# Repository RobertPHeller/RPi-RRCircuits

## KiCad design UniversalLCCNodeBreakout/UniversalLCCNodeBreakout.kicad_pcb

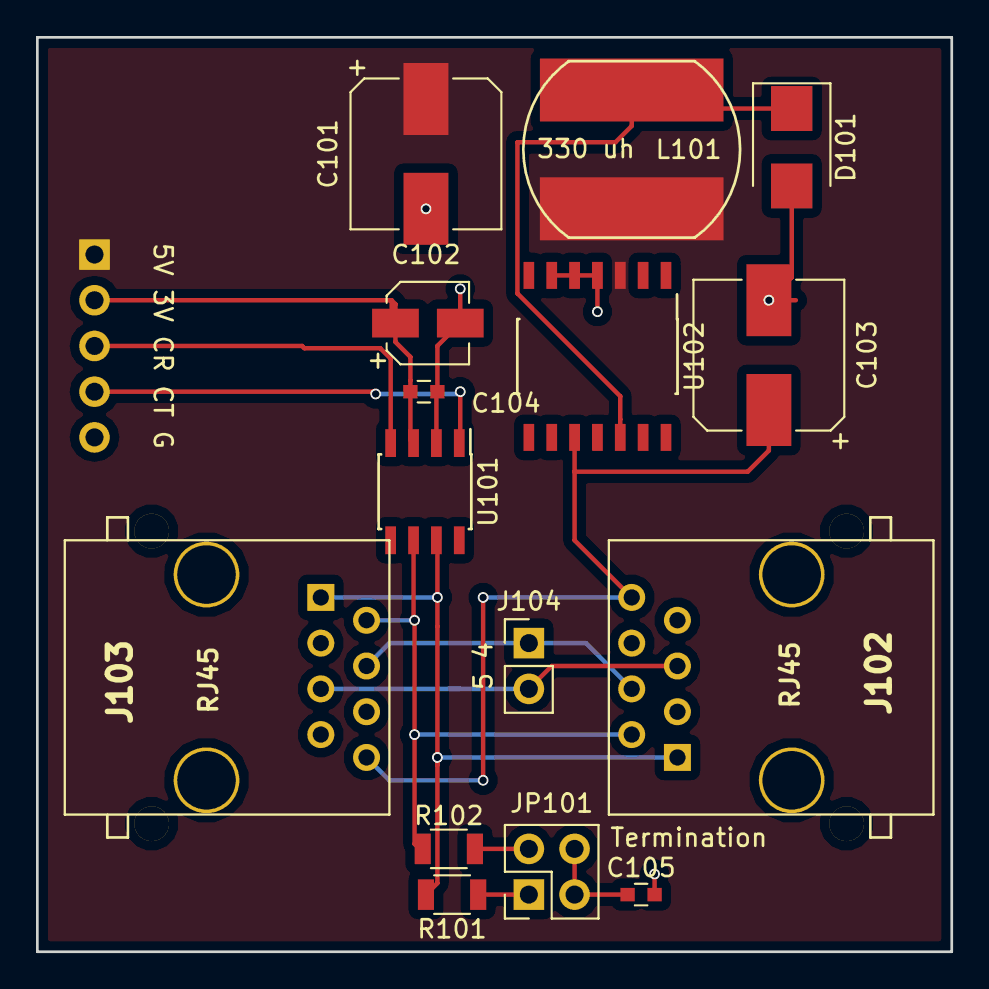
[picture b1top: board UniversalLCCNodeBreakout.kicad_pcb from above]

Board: 2 copper layers, 50.8 x 50.8 mm, 16 parts (1 on the bottom side), 14 nets.

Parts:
C101: 220 uf 25V; CP_Elec_8x10
C102: .1 uf; C_0603
C103: 22 uf 100V; CP_Elec_8x10
C104: 15 uf 15V; CP_Elec_4x5.7
C105: 47 nf; C_0603
D101: CMSH1-60 TR13; D_SMB
J101: 5V 3V CR CT G; Pin_Header_Straight_1x05_Pitch2.54mm
J102, J103: RJ45; RJ45_8N-S
J104: 5 4; Socket_Strip_Straight_1x02_Pitch2.54mm
JP101: Termination; Pin_Header_Straight_2x02_Pitch2.54mm
L101: 330 uh; SRN1060
R101, R102: 60 Ohms; R_1206
U101: TCAN332DR; SOIC-8_3.9x4.9mm_Pitch1.27mm
U102: LM2574N-5; SOIC-14_7.4x8.7mm_Pitch1.27mm

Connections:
+3V3: C102.1, C104.1, J101.2, U101.3
+5V: C101.1, J101.1, L101.2, U102.3
/CANH: J102.1, J103.1, R101.1, U101.7
/CANL: J102.2, J103.2, R102.1, U101.6
/CAN_RX: J101.3, U101.4
/CAN_TX: J101.4, U101.1
CAN +12V: C103.1, J102.8, J103.8, U102.10
GND: C101.2, C102.2, C103.2, C104.2, C105.2, D101.2, J101.5, J102.3, J102.6, J102.7, J103.3, J103.6, J103.7, U101.2, U102.4, U102.5, U102.6
unnamed: C105.1, JP101.3, JP101.4
unnamed: D101.1, L101.1, U102.12
unnamed: J102.4, J103.4, J104.1
unnamed: J102.5, J103.5, J104.2
unnamed: JP101.1, R101.2
unnamed: JP101.2, R102.2

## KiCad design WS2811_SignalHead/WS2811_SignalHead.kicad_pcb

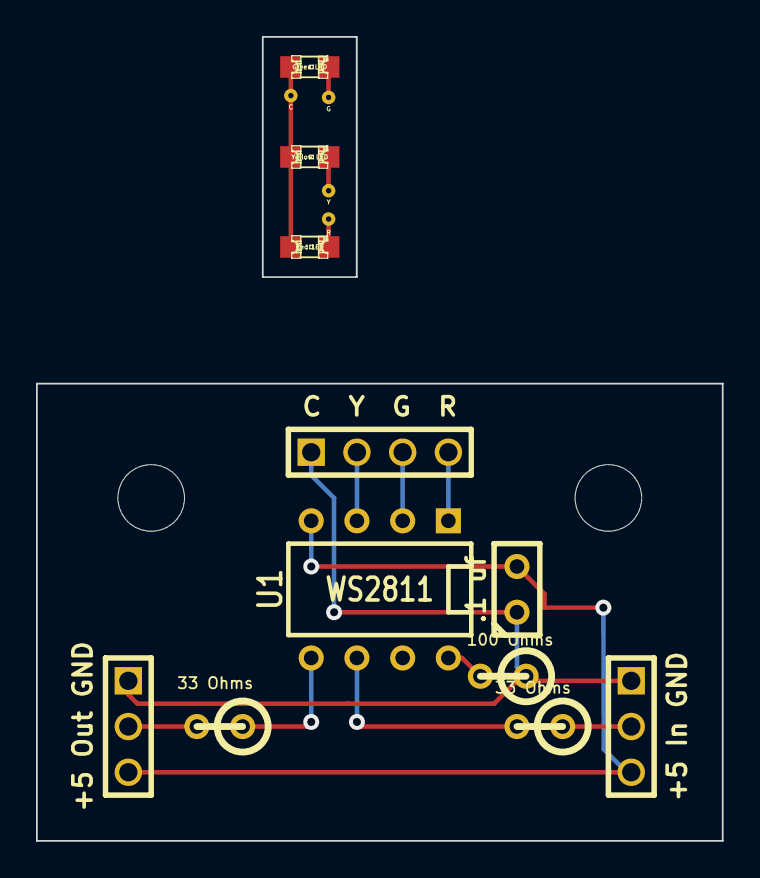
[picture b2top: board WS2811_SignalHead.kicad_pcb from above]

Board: 2 copper layers, 38.1 x 44.7 mm, 17 parts (0 on the bottom side), 14 nets.

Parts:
C1: .1 uf; C1
D1: Red LED; LED-0805
D2: Yellow LED; LED-0805
D3: Green LED; LED-0805
K1: +5 In GND; ScrewTerm_2.54-3
K2: +5 Out GND; ScrewTerm_2.54-3
MH: MountingHole_3-7mm_RevA_Date21Jun2010
MH#2: MountingHole_3-7mm_RevA_Date21Jun2010
P1: C Y G R; ScrewTerm_2.54-4
P2: C; microterm
P3: R; microterm
P4: Y; microterm
P5: G; microterm
R1, R3: 33 Ohms; R1
R2: 100 Ohms; R1
U1: WS2811; DIP-8__300

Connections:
+5V: C1.1, K1.1, K2.1, P1.1, R2.1
Common (+): D1.1, D2.1, D3.1, P2.1
GND: C1.2, K1.3, K2.3, U1.4
Green: D3.2, P5.1
unnamed: R1.2, U1.6
unnamed: K1.2, R1.1
unnamed: K2.2, R3.2
unnamed: R3.1, U1.5
unnamed: R2.2, U1.8
unnamed: P1.2, U1.3
unnamed: P1.3, U1.2
unnamed: P1.4, U1.1
Red: D1.2, P3.1
Yellow: D2.2, P4.1

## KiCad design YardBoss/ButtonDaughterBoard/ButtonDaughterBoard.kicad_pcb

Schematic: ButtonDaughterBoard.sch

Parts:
C1: CP1
C2, C3, C4, C5: .1 uf
C6, C7, C8, C9, C10, C11, C12, C13, C14, C15, C16, C17, C18, C19, C20, C21: 10 nf
J1: I2CIN
J2: I2COUT
P1: 2 1 0
P2: GND 00 01 02 03
P3: GND 17 16 15 14
P4: 13 12 11 10 GND
P5: 04 05 06 07 GND
R1, R2, R3, R4, R5, R6, R7, R8, R9, R10, R11, R12, R13, R14, R15, R16: 10K Ohms
RR1: 10K Ohms
U1: MCP23017
U2, U3, U4: 74HC14

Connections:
+3.3V: C1.1, C2.1, C3.1, C4.1, C5.1, J1.4, J2.2, R1.2, R2.2, R3.2, R4.2, R5.2, R6.2, R7.2, R8.2, R9.2, R10.2, R11.2, R12.2, R13.2, R14.2, R15.2, R16.2, RR1.1 (COM), U1.9 (Vdd), U2.14 (VCC), U3.14 (VCC), U4.14 (VCC)
+5V: J1.5, J2.1
/B0.0: C13.1, P2.4, R8.1, U3.9
/B0.1: C12.1, P2.3, R7.1, U3.5
/B0.2: C11.1, P2.2, R6.1, U3.3
/B0.3: C10.1, P2.1, R5.1, U3.1
/B0.4: C9.1, P5.5, R4.1, U2.13
/B0.5: C8.1, P5.4, R3.1, U2.11
/B0.6: C7.1, P5.3, R2.1, U2.9
/B0.7: C6.1, P5.2, R1.1, U2.5
/B1.0: C21.1, P4.4, R16.1, U4.13
/B1.1: C20.1, P4.3, R15.1, U4.11
/B1.2: C19.1, P4.2, R14.1, U4.9
/B1.3: C18.1, P4.1, R13.1, U4.5
/B1.4: C17.1, P3.5, R12.1, U4.3
/B1.5: C16.1, P3.4, R11.1, U4.1
/B1.6: C15.1, P3.3, R10.1, U3.13
/B1.7: C14.1, P3.2, R9.1, U3.11
GND: C1.2, C2.2, C3.2, C4.2, C5.2, C6.2, C7.2, C8.2, C9.2, C10.2, C11.2, C12.2, C13.2, C14.2, C15.2, C16.2, C17.2, C18.2, C19.2, C20.2, C21.2, J1.1, J2.5, P1.1, P1.3, P1.5, P2.5, P3.1, P4.5, P5.1, U1.10 (Vss), U2.1, U2.3, U2.7 (GND), U3.7 (GND), U4.7 (GND)
unnamed: U1.2 (GP1.1), U4.10
unnamed: U1.3 (GP1.2), U4.8
unnamed: U1.4 (GP1.3), U4.6
unnamed: U1.5 (GP1.4), U4.4
unnamed: U1.6 (GP1.5), U4.2
unnamed: U1.7 (GP1.6), U3.12
unnamed: U1.8 (GP1.7), U3.10
unnamed: U1.21 (GP0.0), U3.8
unnamed: U1.22 (GP0.1), U3.6
unnamed: U1.23 (GP0.2), U3.4
unnamed: U1.1 (Gp1.0), U4.12
unnamed: P1.2, RR1.3, U1.17 (A2)
unnamed: P1.4, RR1.4, U1.16 (A1)
unnamed: P1.6, RR1.5, U1.15 (A0)
unnamed: U1.24 (GP0.3), U3.2
unnamed: U1.25 (GP0.4), U2.12
unnamed: U1.26 (GP0.5), U2.10
unnamed: U1.27 (GP0.6), U2.8
unnamed: U1.28 (GP0.7), U2.6
unnamed: RR1.2, U1.18 (Reset)
SCL: J1.2, J2.4, U1.12 (SCL)
SDA: J1.3, J2.3, U1.13 (SDA)

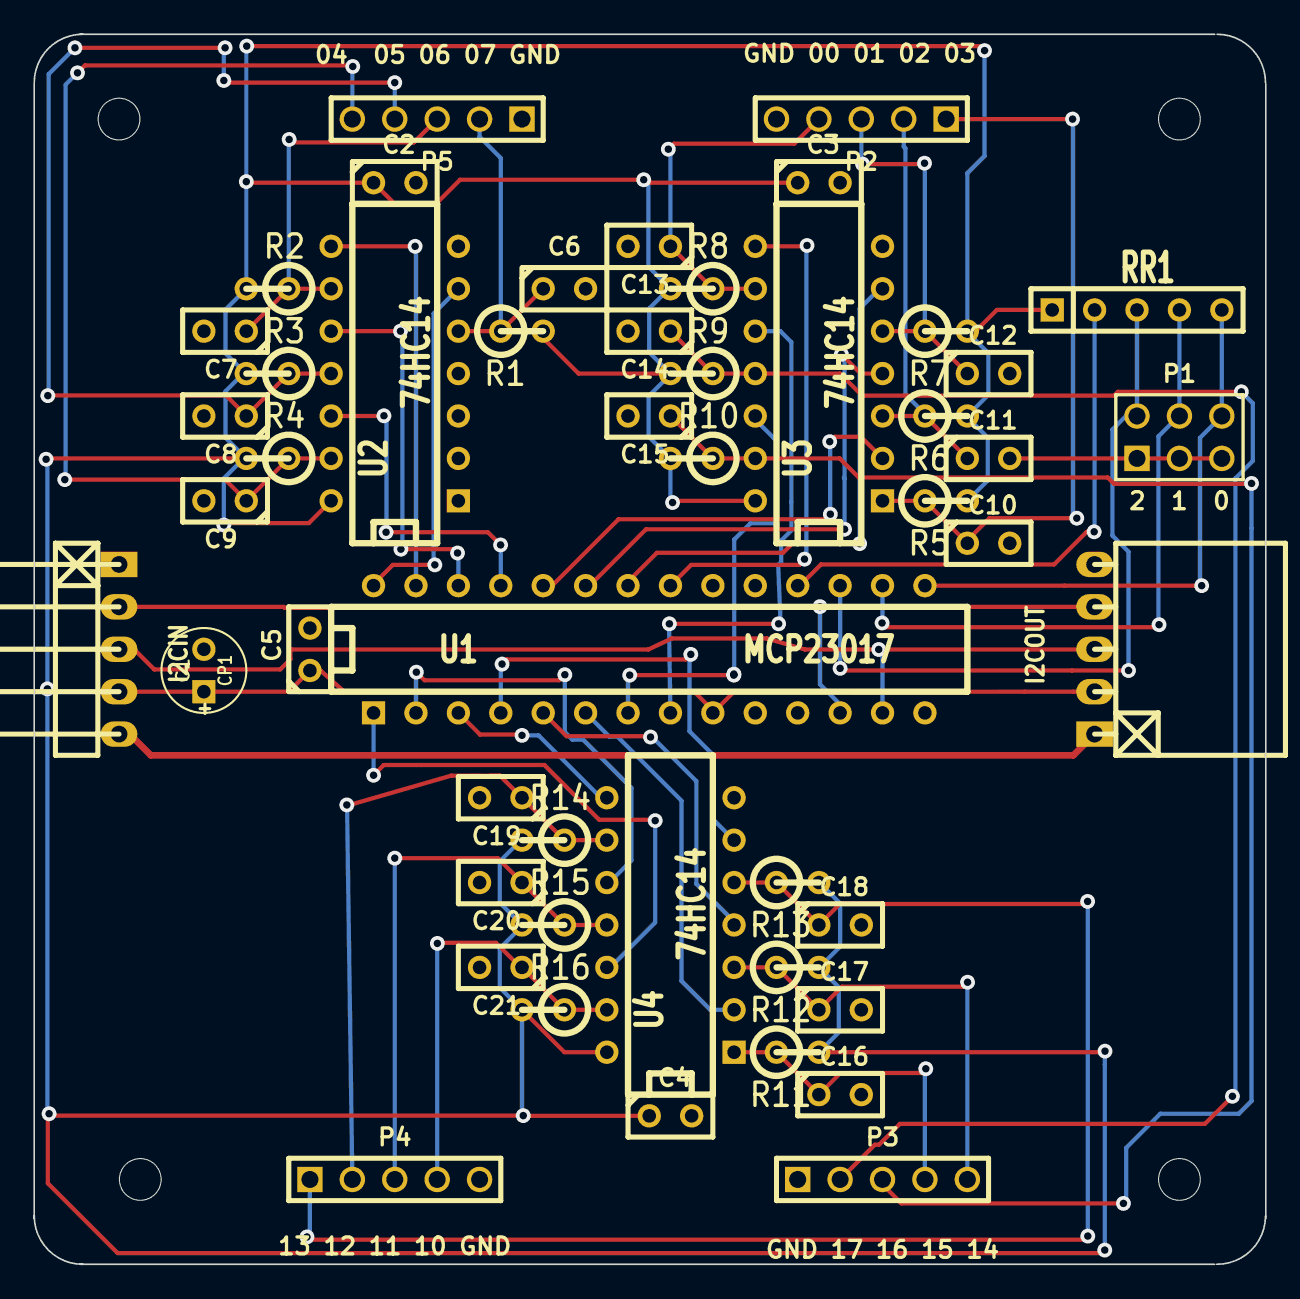
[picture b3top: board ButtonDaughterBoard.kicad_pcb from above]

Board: 2 copper layers, 73.8 x 73.7 mm, 53 parts (0 on the bottom side), 41 nets.

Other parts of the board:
MH: MountingHole_2-5mm_RevA_Date21Jun2010
MH#2, MH#3, MH#4: MountingHole_2-5mm_RevA_Date21Jun2010

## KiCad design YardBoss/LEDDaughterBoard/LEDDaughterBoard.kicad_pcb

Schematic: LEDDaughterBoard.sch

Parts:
C1: .1 uf
C2: 10 uf
C3: 15 uf
J1: I2CIN
J2: I2COUT
P1: 2 1 0
P2: L04 L05 L06 L07 C
P3: C L14 L15 L16 L17
P4: L00 L01 L02 L03 C
P5: C L13 L12 L11 L10
Q1, Q2, Q3, Q4: MPQ2222A; TO116
R1, R2, R3, R4, R9, R10, R11, R12, R17, R18, R19, R20, R25, R26, R27, R28: 1K Ohms
R5, R6, R7, R8, R13, R14, R15, R16, R21, R22, R23, R24, R29, R30, R31, R32: 150 Ohms
RR1: 10K Ohms
U1: MCP23017

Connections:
+3.3V: C1.1, C2.1, J1.4, J2.2, RR1.1 (COM), U1.9 (Vdd)
+5V: C3.1, J1.5, J2.1, P2.1, P3.1, P4.1, P5.1
/L00: P4.5, R16.2
/L01: P4.4, R15.2
/L02: P4.3, R14.2
/L03: P4.2, R13.2
/L04: P2.5, R8.2
/L05: P2.4, R7.2
/L06: P2.3, R6.2
/L07: P2.2, R5.2
/L10: P5.5, R32.2
/L11: P5.4, R31.2
/L12: P5.3, R30.2
/L13: P5.2, R29.2
/L14: P3.5, R24.2
/L15: P3.4, R23.2
/L16: P3.3, R22.2
/L17: P3.2, R21.2
GND: C1.2, C2.2, C3.2, J1.1, J2.5, P1.1, P1.3, P1.5, Q1.3 (E), Q1.5 (E), Q1.10 (E), Q1.12 (E), Q2.3 (E), Q2.5 (E), Q2.10 (E), Q2.12 (E), Q3.3 (E), Q3.5 (E), Q3.10 (E), Q3.12 (E), Q4.3 (E), Q4.5 (E), Q4.10 (E), Q4.12 (E), U1.10 (Vss)
unnamed: RR1.2, U1.18 (Reset)
unnamed: R9.1, U1.24 (GP0.3)
unnamed: R4.1, U1.25 (GP0.4)
unnamed: R3.1, U1.26 (GP0.5)
unnamed: R2.1, U1.27 (GP0.6)
unnamed: R1.1, U1.28 (GP0.7)
unnamed: Q4.7 (C), R30.1
unnamed: Q4.1 (C), R29.1
unnamed: Q4.13 (B), R28.2
unnamed: Q4.9 (B), R27.2
unnamed: Q4.6 (B), R26.2
unnamed: Q4.2 (B), R25.2
unnamed: R28.1, U1.1 (Gp1.0)
unnamed: R27.1, U1.2 (GP1.1)
unnamed: R26.1, U1.3 (GP1.2)
unnamed: R25.1, U1.4 (GP1.3)
unnamed: Q4.14 (C), R32.1
unnamed: Q4.8 (C), R31.1
unnamed: P1.6, RR1.5, U1.15 (A0)
unnamed: P1.4, RR1.4, U1.16 (A1)
unnamed: P1.2, RR1.3, U1.17 (A2)
unnamed: R18.1, U1.7 (GP1.6)
unnamed: R17.1, U1.8 (GP1.7)
unnamed: R12.1, U1.21 (GP0.0)
unnamed: R11.1, U1.22 (GP0.1)
unnamed: R10.1, U1.23 (GP0.2)
unnamed: R20.1, U1.5 (GP1.4)
unnamed: R19.1, U1.6 (GP1.5)
unnamed: Q1.9 (B), R3.2
unnamed: Q1.6 (B), R2.2
unnamed: Q1.2 (B), R1.2
unnamed: Q1.1 (C), R5.1
unnamed: Q1.8 (C), R7.1
unnamed: Q1.7 (C), R6.1
unnamed: Q1.13 (B), R4.2
unnamed: Q1.14 (C), R8.1
unnamed: Q3.13 (B), R20.2
unnamed: Q3.9 (B), R19.2
unnamed: Q3.6 (B), R18.2
unnamed: Q3.2 (B), R17.2
unnamed: Q3.14 (C), R24.1
unnamed: Q3.8 (C), R23.1
unnamed: Q3.7 (C), R22.1
unnamed: Q3.1 (C), R21.1
unnamed: Q2.14 (C), R16.1
unnamed: Q2.13 (B), R12.2
unnamed: Q2.9 (B), R11.2
unnamed: Q2.8 (C), R15.1
unnamed: Q2.7 (C), R14.1
unnamed: Q2.6 (B), R10.2
unnamed: Q2.2 (B), R9.2
unnamed: Q2.1 (C), R13.1
SCL: J1.2, J2.4, U1.12 (SCL)
SDA: J1.3, J2.3, U1.13 (SDA)

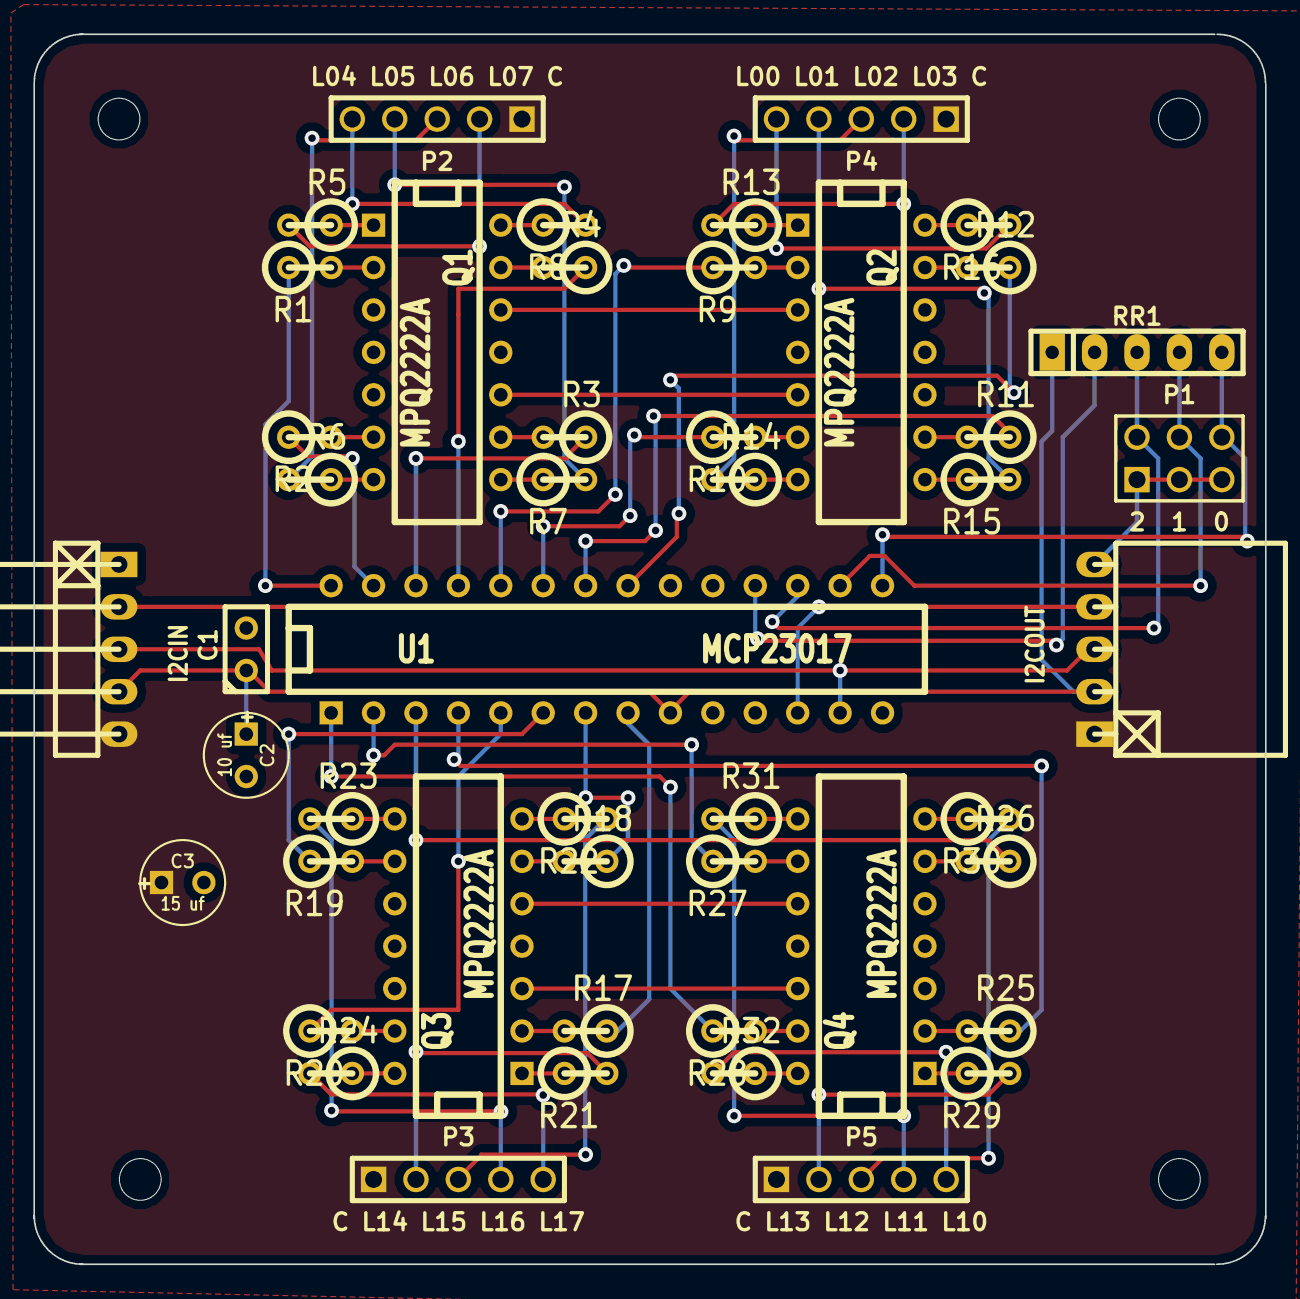
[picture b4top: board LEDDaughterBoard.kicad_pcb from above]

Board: 2 copper layers, 73.8 x 73.7 mm, 52 parts (0 on the bottom side), 73 nets.

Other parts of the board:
MH: MountingHole_2-5mm_RevA_Date21Jun2010
MH#2, MH#3, MH#4: MountingHole_2-5mm_RevA_Date21Jun2010

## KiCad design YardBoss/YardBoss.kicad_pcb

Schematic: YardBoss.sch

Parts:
J1: RPI_GPIO
P1: CE0
P2: CE1
P3: CS
P4: I2C Expansion; Mouser Part Number 437-8018700520001101
P6, P7: CONN_5

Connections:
+3.3V: J1.1, J1.17, P4.2, P6.1; also elsewhere on the board
+5V: J1.2, J1.4, P4.1; also elsewhere on the board
/CAN Transciver/CS: P3.1; also elsewhere on the board
/CAN Transciver/INT: J1.32; also elsewhere on the board
/Stall Motors 1/M Select 2: J1.12; also elsewhere on the board
/Stall Motors 1/MSelect 1: J1.11; also elsewhere on the board
/Stall Motors 1/Point Sense 1: J1.13; also elsewhere on the board
/Stall Motors 1/Point Sense 2: J1.15; also elsewhere on the board
/Stall Motors 2/M Select 2: J1.18; also elsewhere on the board
/Stall Motors 2/MSelect 1: J1.16; also elsewhere on the board
/Stall Motors 2/Point Sense 1: J1.22; also elsewhere on the board
/Stall Motors 2/Point Sense 2: J1.7; also elsewhere on the board
/Wiring Pi 21: J1.29, P6.2
/Wiring Pi 22: J1.31, P6.3
/Wiring Pi 23: J1.33, P6.4
/Wiring Pi 24: J1.35, P6.5
/Wiring Pi 25: J1.37, P7.1
/Wiring Pi 27: J1.36, P7.2
/Wiring Pi 28: J1.38, P7.3
/Wiring Pi 29: J1.40, P7.4
GND: J1.6, J1.9, J1.14, J1.20, J1.25, J1.30, J1.34, J1.39, P4.5, P7.5; also elsewhere on the board
MISO: J1.21; also elsewhere on the board
MOSI: J1.19; also elsewhere on the board
unnamed: J1.24, P1.1
unnamed: J1.26, P2.1
SCL: J1.5, P4.4
SCLK: J1.23; also elsewhere on the board
SDA: J1.3, P4.3

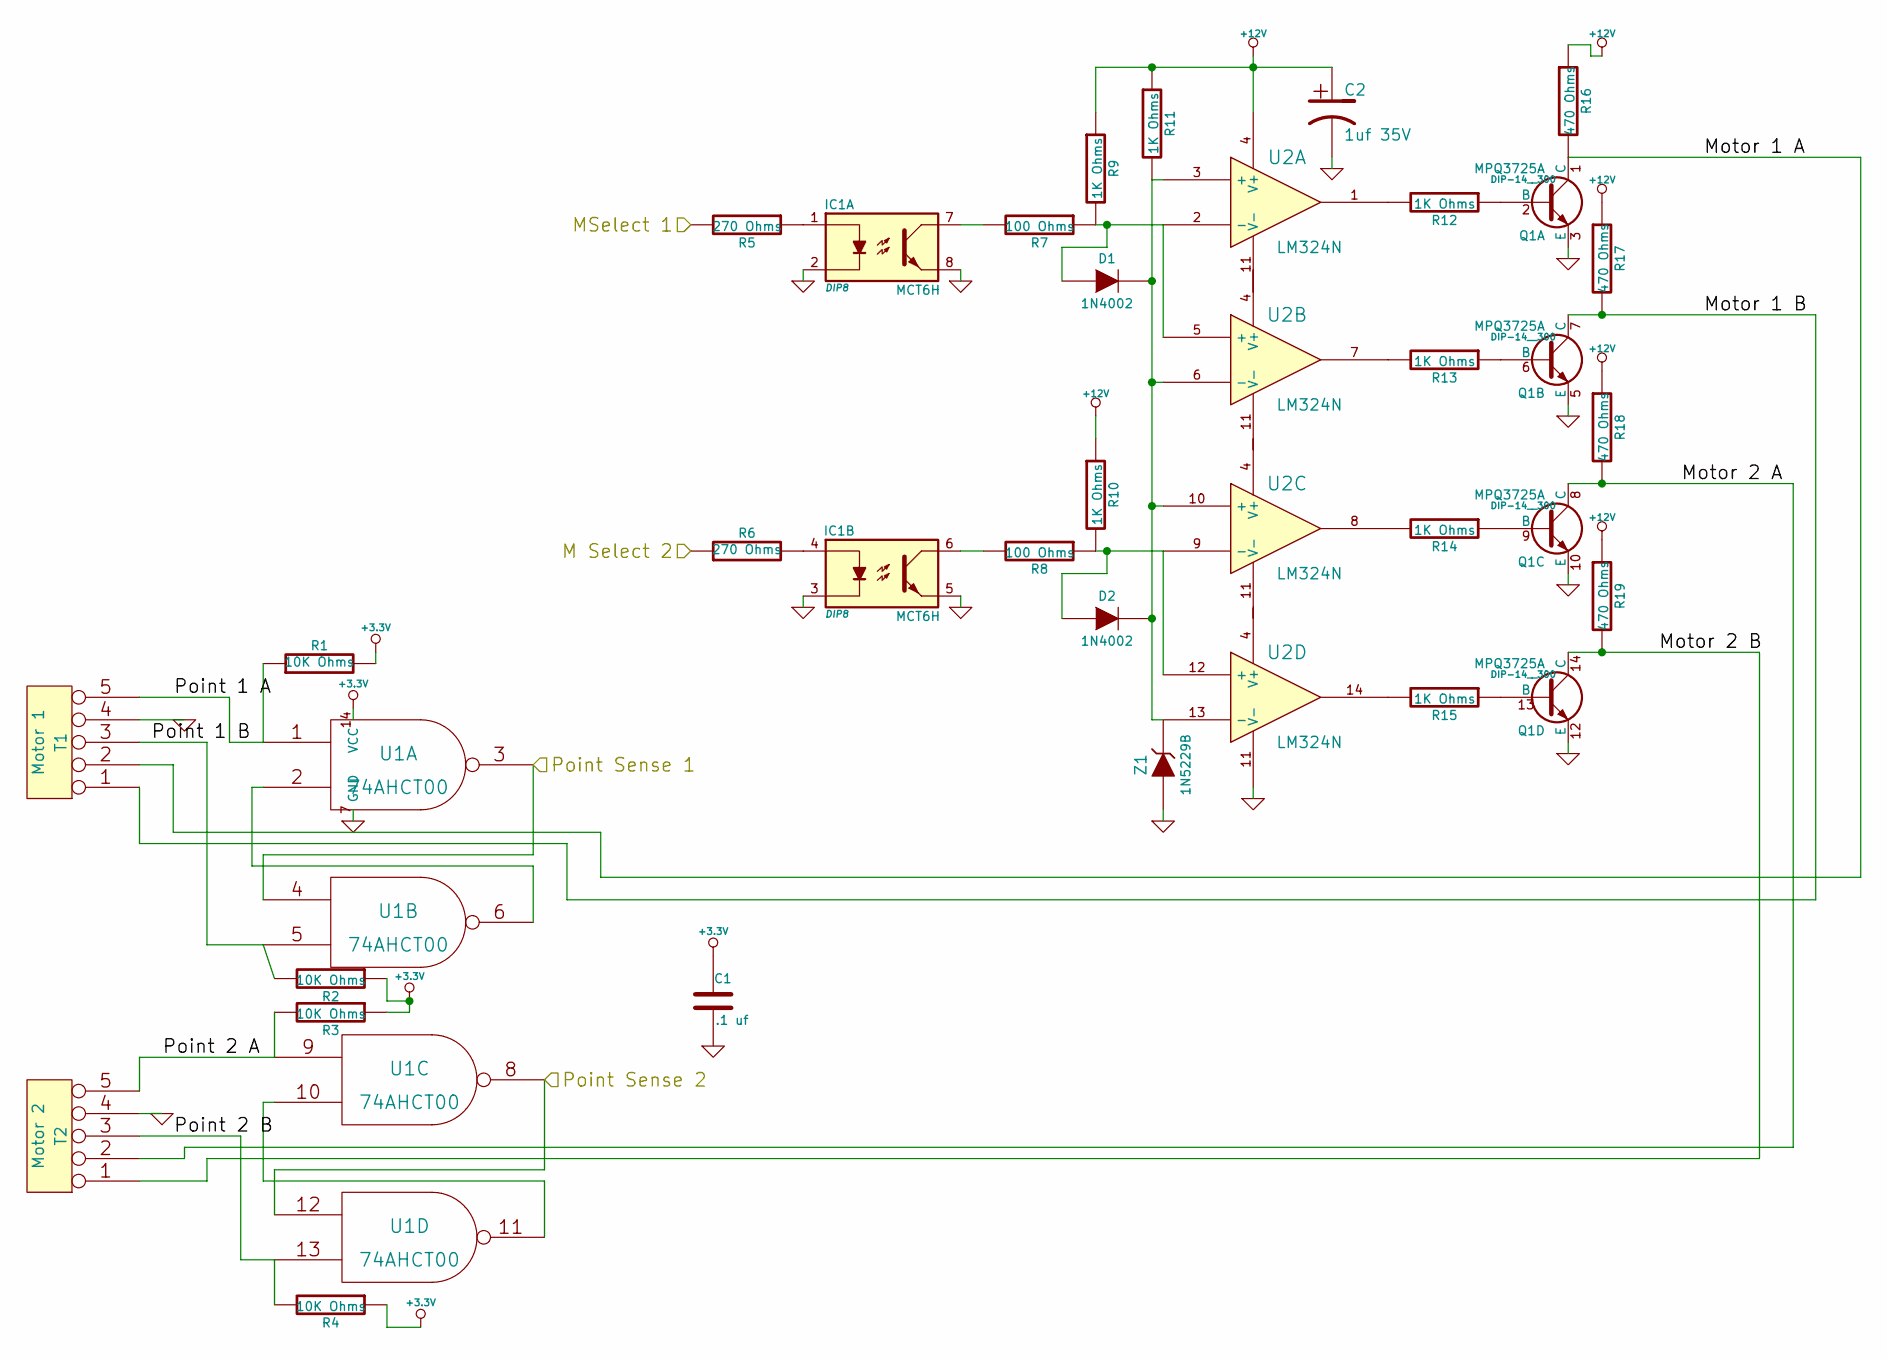
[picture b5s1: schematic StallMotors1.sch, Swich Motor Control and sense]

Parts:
C1: .1 uf; Mouser part Number 21RZ310-RC
C2: 1uf 35V; Mouser Part Number 74-199D105X9035A1VE3
D1, D2: 1N4002; Mouser Part Number 833-1N4002-TP
IC1: MCT6H; DIP8; Mouser part Number 782-MCT6H
Q1: MPQ3725A; DIP-14__300; Mouser part Number 610-MPQ3725A
R1, R2, R3, R4: 10K Ohms; Mouser Part Number 603-CFR-25JR-5210K
R5, R6: 270 Ohms; Mouser Part Number 603-CFR-25JR-52-270R
R7, R8: 100 Ohms; Mouser Part Number 603-CFR-25JR-52100R
R9: 1K Ohms; Mouser part Number 279-2-1623927-3
R10, R11, R12, R13, R14, R15: 1K Ohms; Mouser Part Number 279-2-1623927-3
R16: 470 Ohms; Mouser part Number 279-CFR50J470R
R17, R18: 470 Ohms; Mouser Part Number 279-CFR50J470R
R19: 470 Ohms; Mousere Part Number 279-CFR50J470R
T1: Motor 1; Mouser Part Number 571-282834-5
T2: Motor 2; Mouser Part Number 571-282834-5
U1: 74AHCT00; Mouser part Number 595-SN74AHC00N
U2: LM324N; Mouser part Number 512-LM324N
Z1: 1N5229B; Mouser Part Number 512-1N5229BTR

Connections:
+3.3V: C1.1, R1.2, R2.1, R3.1, R4.1, U1.14 (VCC); also elsewhere on the board
+12V: C2.1, R9.1, R10.1, R11.1, R16.1, R17.1, R18.1, R19.1, U2.4 (V+); also elsewhere on the board
/Stall Motors 1/M Select 2: R6.1; also elsewhere on the board
/Stall Motors 1/MSelect 1: R5.2; also elsewhere on the board
/Stall Motors 1/Motor 1 A: Q1.1 (C), R16.2, T1.2
/Stall Motors 1/Motor 1 B: Q1.7 (C), R17.2, T1.1
/Stall Motors 1/Motor 2 A: Q1.8 (C), R18.2, T2.2
/Stall Motors 1/Motor 2 B: Q1.14 (C), R19.2, T2.1
/Stall Motors 1/Point 1 A: R1.1, T1.5, U1.1
/Stall Motors 1/Point 1 B: R2.2, T1.3, U1.5
/Stall Motors 1/Point 2 A: R3.2, T2.5, U1.9
/Stall Motors 1/Point 2 B: R4.2, T2.3, U1.13
/Stall Motors 1/Point Sense 1: U1.3, U1.4; also elsewhere on the board
/Stall Motors 1/Point Sense 2: U1.8, U1.12; also elsewhere on the board
GND: C1.2, C2.2, IC1.2, IC1.3, IC1.5, IC1.8, Q1.3 (E), Q1.5 (E), Q1.10 (E), Q1.12 (E), T1.4, T2.4, U1.7 (GND), U2.11 (V-), Z1.1 (A); also elsewhere on the board
unnamed: Q1.6 (B), R13.1
unnamed: Q1.2 (B), R12.1
unnamed: R12.2, U2.1
unnamed: R13.2, U2.7
unnamed: R14.2, U2.8
unnamed: Q1.9 (B), R14.1
unnamed: R15.2, U2.14
unnamed: Q1.13 (B), R15.1
unnamed: D2.1 (A), R8.1, R10.2, U2.9 (-), U2.12 (+)
unnamed: IC1.6, R8.2
unnamed: IC1.4, R6.2
unnamed: IC1.1, R5.1
unnamed: IC1.7, R7.2
unnamed: U1.2, U1.6
unnamed: U1.10, U1.11
unnamed: D1.1 (A), R7.1, R9.2, U2.2 (-), U2.5 (+)
unnamed: D1.2 (K), D2.2 (K), R11.2, U2.3 (+), U2.6 (-), U2.10 (+), U2.13 (-), Z1.2 (K)

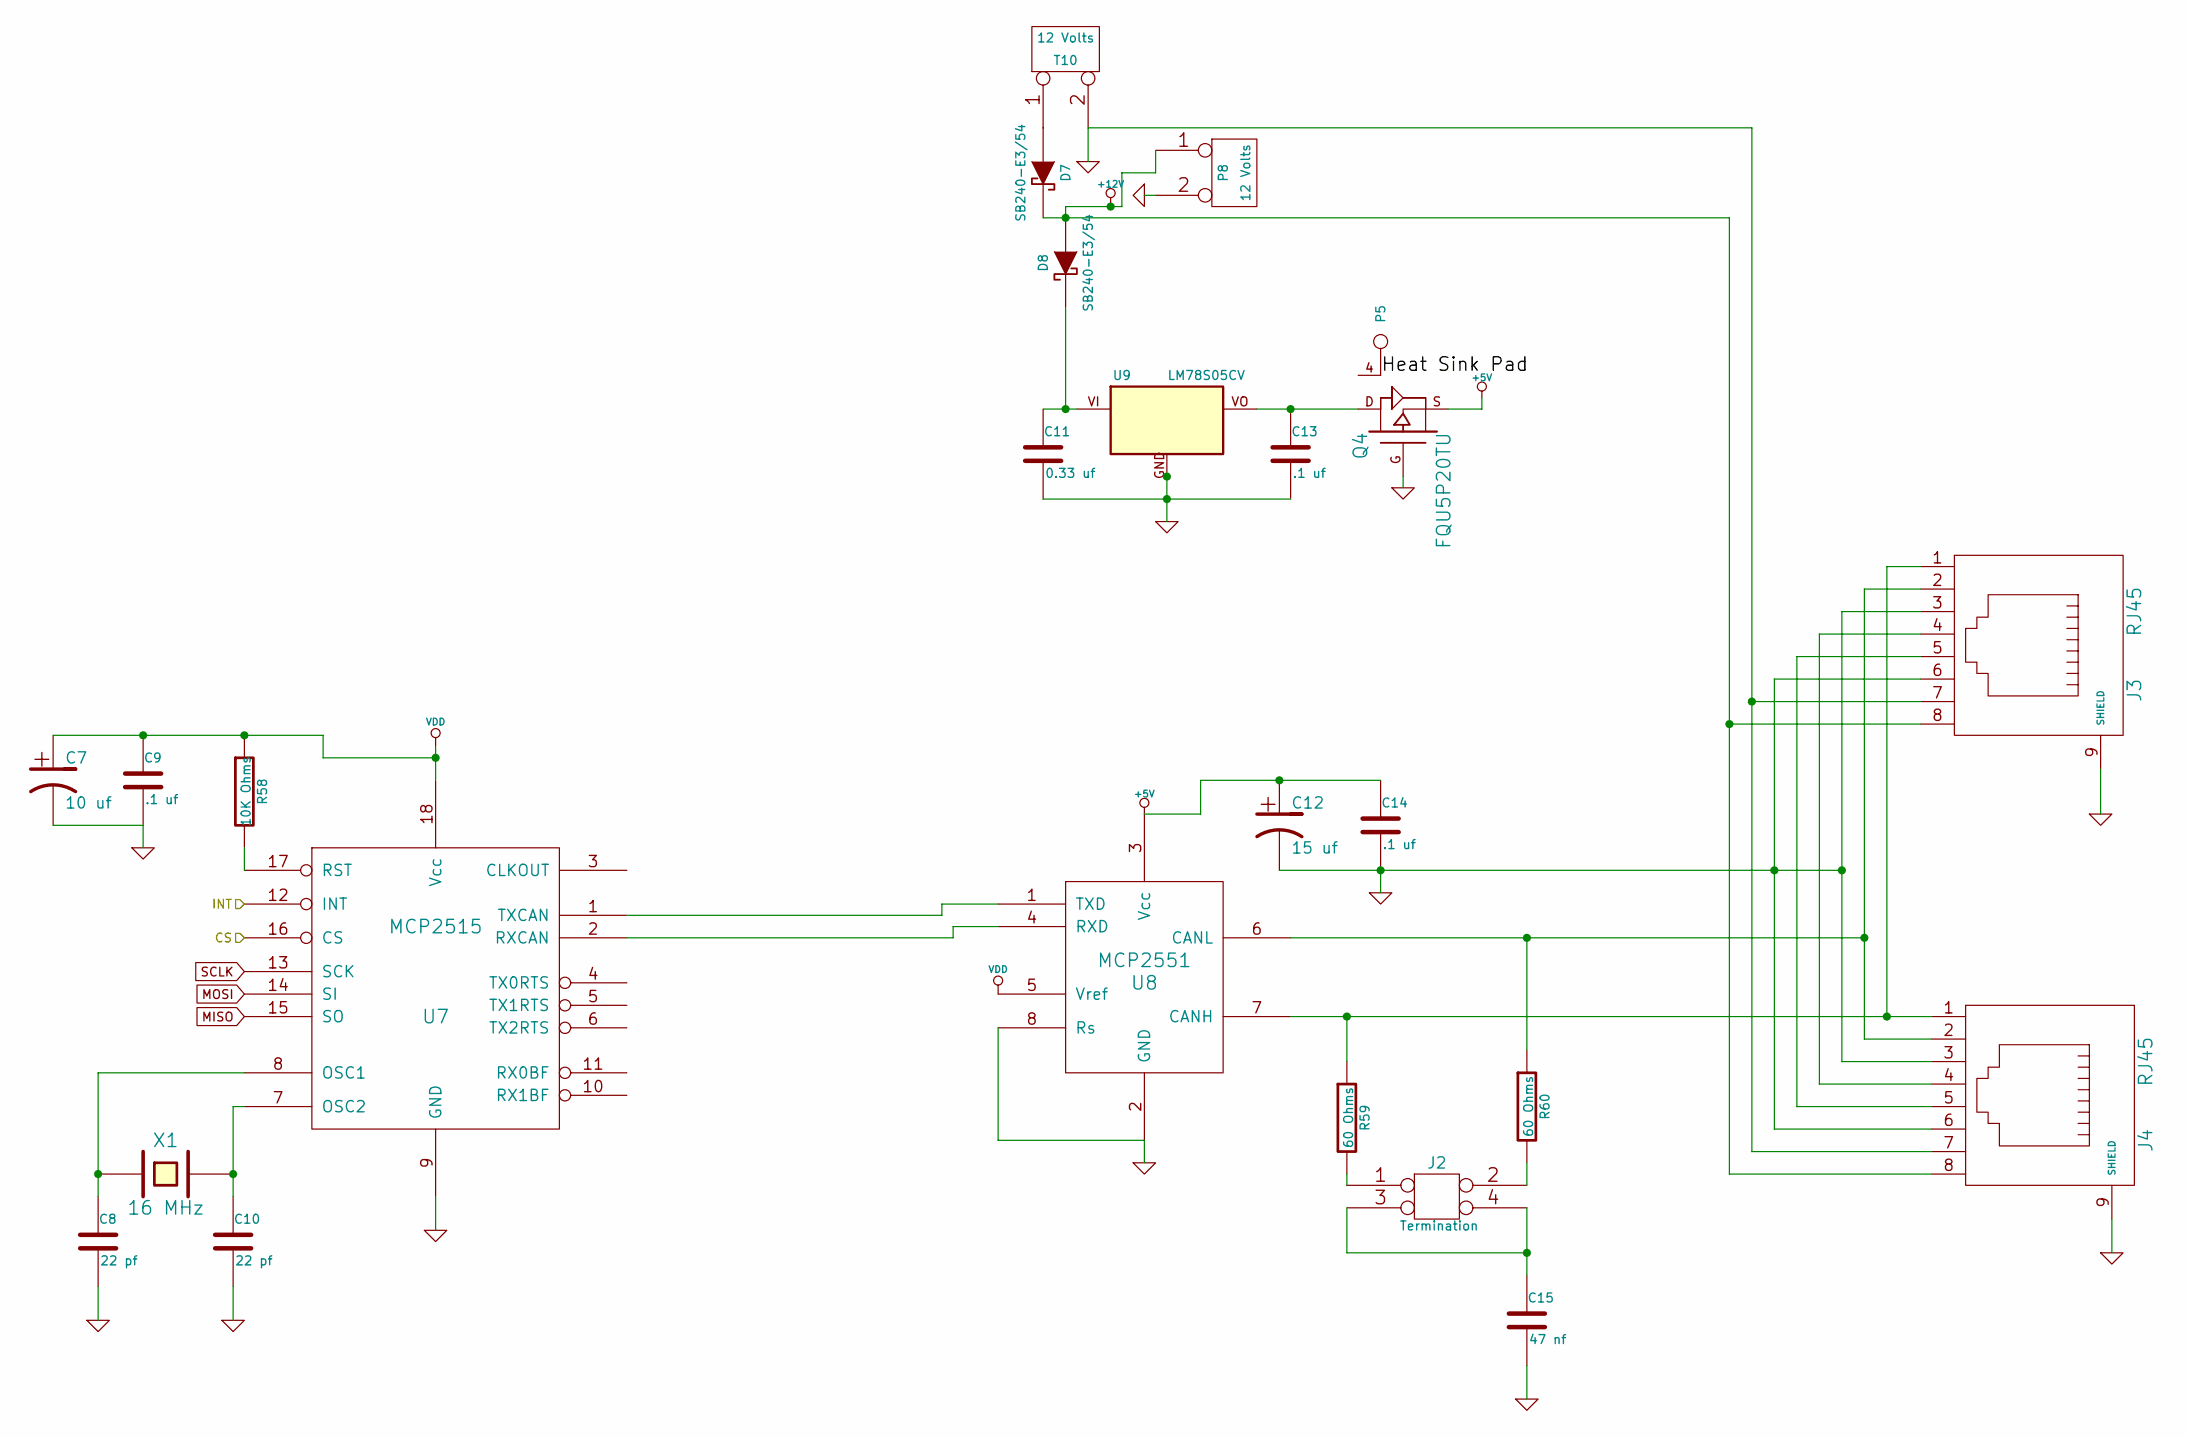
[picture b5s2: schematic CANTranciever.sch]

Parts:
C7: 10 uf; C1V5; Mouser part Number 667-ECA-1HM100I
C8, C10: 22 pf; C2; Mouser part number 594-K220J10C0GF5UH5
C9: .1 uf; C1; Mouser Part Number 21RZ310-RC
C11: 0.33 uf; Mouser Part Number 75-1C10Z5U334M050B
C12: 15 uf; C1V7; Mouser part number 667-EEA-GA1H150
C13: .1 uf; Mouser Part Number 21RZ310-RC
C14: .1 uf; C1; Mouser Part number 21RZ310-RC
C15: 47 nf; Mouser Part Number 75-1C10Z5U473M050B
D7, D8: SB240-E3/54; Mouser Part Number 625-SB240-E3
J2: Termination; Mouser Part Number 649-67997-404HLF
J3, J4: RJ45; RJ45-8N-S; Mouser part number 592-RJ45-8N-S
P5: CONN_1
P8: 12 Volts
Q4: FQU5P20TU; TO-251-3; Mouser Part Number 512-FQU5P20TU
R58: 10K Ohms; R1; Mouser part number 603-CFR-25JR-5210K
R59, R60: 60 Ohms; Mouser Part Number 71-RN60C60R0B/R
T10: 12 Volts; Mouser Part Number 571-1776118-2
U7: MCP2515; DIP-18_300; Mouser part number 579-MCP2515-I/P
U8: MCP2551; DIP-8_300; Mouser part number 579-MCP2551-I/P
U9: LM78S05CV; LM78XXV
X1: 16 MHz; HC-49V; Mouser part number 449-LFXTAL027945BULK

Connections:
+3.3V: C7.1, C9.1, R58.1, U7.18 (Vcc), U8.5 (Vref); also elsewhere on the board
+5V: C12.1, C14.1, Q4.S, U8.3 (Vcc); also elsewhere on the board
+12V: D7.2 (K), D8.1 (A), J3.8, J4.8, P8.1; also elsewhere on the board
/CAN Transciver/CS: U7.16 (CS); also elsewhere on the board
/CAN Transciver/Heat Sink Pad: P5.1, Q4.4 (Heat_Sink_Pad)
/CAN Transciver/INT: U7.12 (INT); also elsewhere on the board
GND: C7.2, C8.2, C9.2, C10.2, C11.2, C12.2, C13.2, C14.2, C15.2, J3.3, J3.6, J3.7, J3.9 (SHIELD), J4.3, J4.6, J4.7, J4.9 (SHIELD), P8.2 (PM), Q4.G, T10.2 (PM), U7.9 (GND), U8.2 (GND), U8.8 (Rs), U9.GND; also elsewhere on the board
MISO: U7.15 (SO); also elsewhere on the board
MOSI: U7.14 (SI); also elsewhere on the board
unnamed: R58.2, U7.17 (RST)
unnamed: C10.1, U7.7 (OSC2), X1.2
unnamed: C8.1, U7.8 (OSC1), X1.1
unnamed: U7.2 (RXCAN), U8.4 (RXD)
unnamed: U7.1 (TXCAN), U8.1 (TXD)
unnamed: J3.5, J4.5
unnamed: J3.4, J4.4
unnamed: J3.1, J4.1, R59.1, U8.7 (CANH)
unnamed: J3.2, J4.2, R60.1, U8.6 (CANL)
unnamed: C15.1, J2.3, J2.4
unnamed: J2.1, R59.2
unnamed: J2.2, R60.2
unnamed: C11.1, D8.2 (K), U9.VI
unnamed: D7.1 (A), T10.1
unnamed: C13.1, Q4.D, U9.VO
SCLK: U7.13 (SCK); also elsewhere on the board

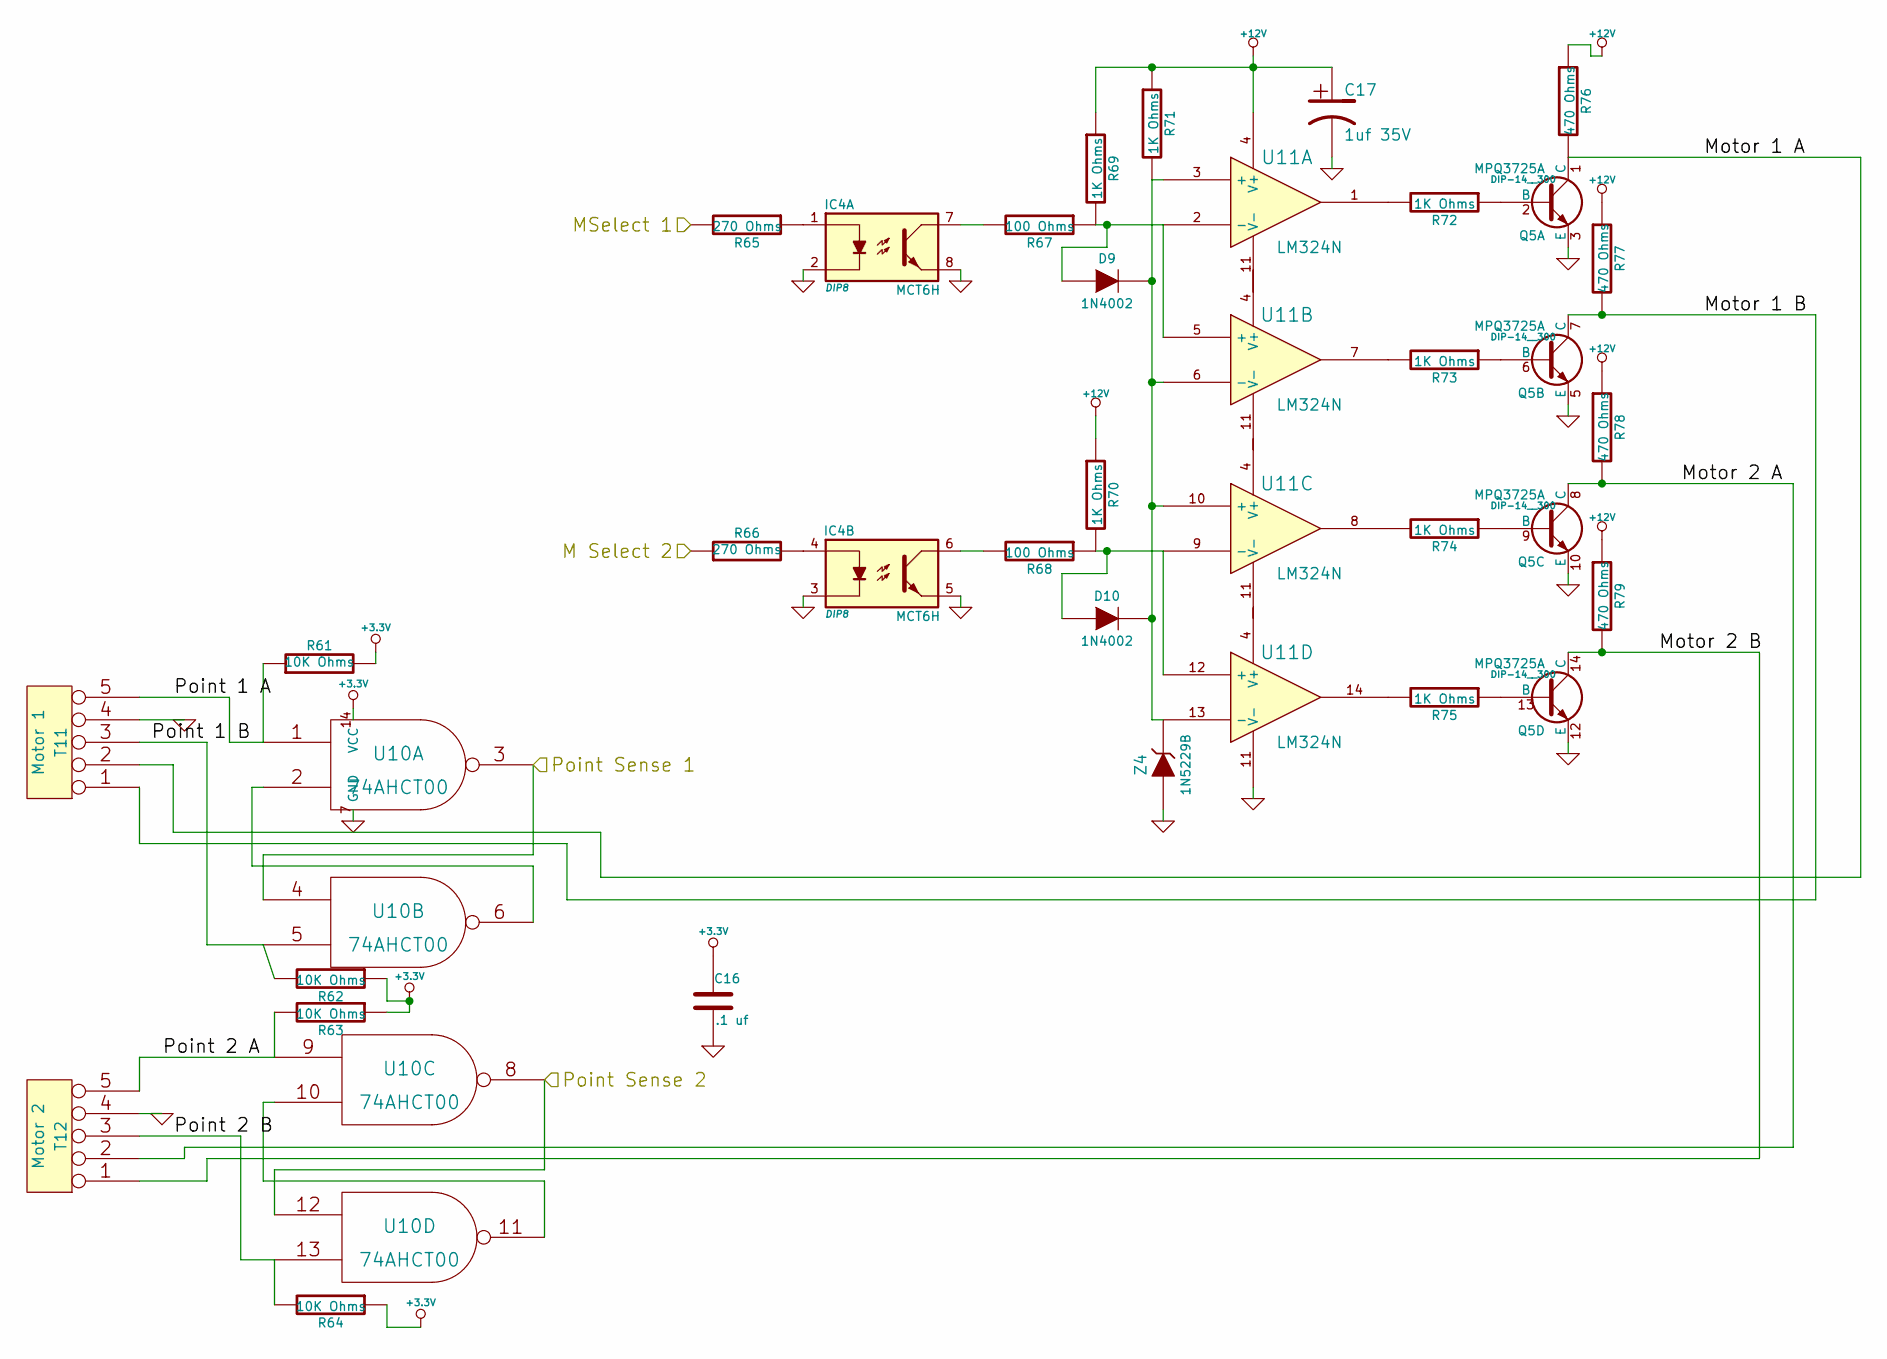
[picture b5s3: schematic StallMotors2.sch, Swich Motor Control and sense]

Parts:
C16: .1 uf; Mouser part Number 21RZ310-RC
C17: 1uf 35V; Mouser Part Number 74-199D105X9035A1VE3
D9, D10: 1N4002; Mouser Part Number 833-1N4002-TP
IC4: MCT6H; DIP8; Mouser part Number 782-MCT6H
Q5: MPQ3725A; DIP-14__300; Mouser part Number 610-MPQ3725A
R61, R62, R63, R64: 10K Ohms; Mouser Part Number 603-CFR-25JR-5210K
R65, R66: 270 Ohms; Mouser Part Number 603-CFR-25JR-52-270R
R67, R68: 100 Ohms; Mouser Part Number 603-CFR-25JR-52100R
R69: 1K Ohms; Mouser part Number 279-2-1623927-3
R70, R71, R72, R73, R74, R75: 1K Ohms; Mouser Part Number 279-2-1623927-3
R76: 470 Ohms; Mouser part Number 279-CFR50J470R
R77, R78: 470 Ohms; Mouser Part Number 279-CFR50J470R
R79: 470 Ohms; Mousere Part Number 279-CFR50J470R
T11: Motor 1; Mouser Part Number 571-282834-5
T12: Motor 2; Mouser Part Number 571-282834-5
U10: 74AHCT00; Mouser part Number 595-SN74AHC00N
U11: LM324N; Mouser part Number 512-LM324N
Z4: 1N5229B; Mouser Part Number 512-1N5229BTR

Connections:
+3.3V: C16.1, R61.2, R62.1, R63.1, R64.1, U10.14 (VCC); also elsewhere on the board
+12V: C17.1, R69.1, R70.1, R71.1, R76.1, R77.1, R78.1, R79.1, U11.4 (V+); also elsewhere on the board
/Stall Motors 2/M Select 2: R66.1; also elsewhere on the board
/Stall Motors 2/MSelect 1: R65.2; also elsewhere on the board
/Stall Motors 2/Motor 1 A: Q5.1 (C), R76.2, T11.2
/Stall Motors 2/Motor 1 B: Q5.7 (C), R77.2, T11.1
/Stall Motors 2/Motor 2 A: Q5.8 (C), R78.2, T12.2
/Stall Motors 2/Motor 2 B: Q5.14 (C), R79.2, T12.1
/Stall Motors 2/Point 1 A: R61.1, T11.5, U10.1
/Stall Motors 2/Point 1 B: R62.2, T11.3, U10.5
/Stall Motors 2/Point 2 A: R63.2, T12.5, U10.9
/Stall Motors 2/Point 2 B: R64.2, T12.3, U10.13
/Stall Motors 2/Point Sense 1: U10.3, U10.4; also elsewhere on the board
/Stall Motors 2/Point Sense 2: U10.8, U10.12; also elsewhere on the board
GND: C16.2, C17.2, IC4.2, IC4.3, IC4.5, IC4.8, Q5.3 (E), Q5.5 (E), Q5.10 (E), Q5.12 (E), T11.4, T12.4, U10.7 (GND), U11.11 (V-), Z4.1 (A); also elsewhere on the board
unnamed: R75.2, U11.14
unnamed: R74.2, U11.8
unnamed: R73.2, U11.7
unnamed: D10.1 (A), R68.1, R70.2, U11.9 (-), U11.12 (+)
unnamed: D9.1 (A), R67.1, R69.2, U11.2 (-), U11.5 (+)
unnamed: IC4.7, R67.2
unnamed: IC4.4, R66.2
unnamed: IC4.1, R65.1
unnamed: IC4.6, R68.2
unnamed: U10.10, U10.11
unnamed: R72.2, U11.1
unnamed: D9.2 (K), D10.2 (K), R71.2, U11.3 (+), U11.6 (-), U11.10 (+), U11.13 (-), Z4.2 (K)
unnamed: Q5.2 (B), R72.1
unnamed: Q5.6 (B), R73.1
unnamed: Q5.9 (B), R74.1
unnamed: Q5.13 (B), R75.1
unnamed: U10.2, U10.6
